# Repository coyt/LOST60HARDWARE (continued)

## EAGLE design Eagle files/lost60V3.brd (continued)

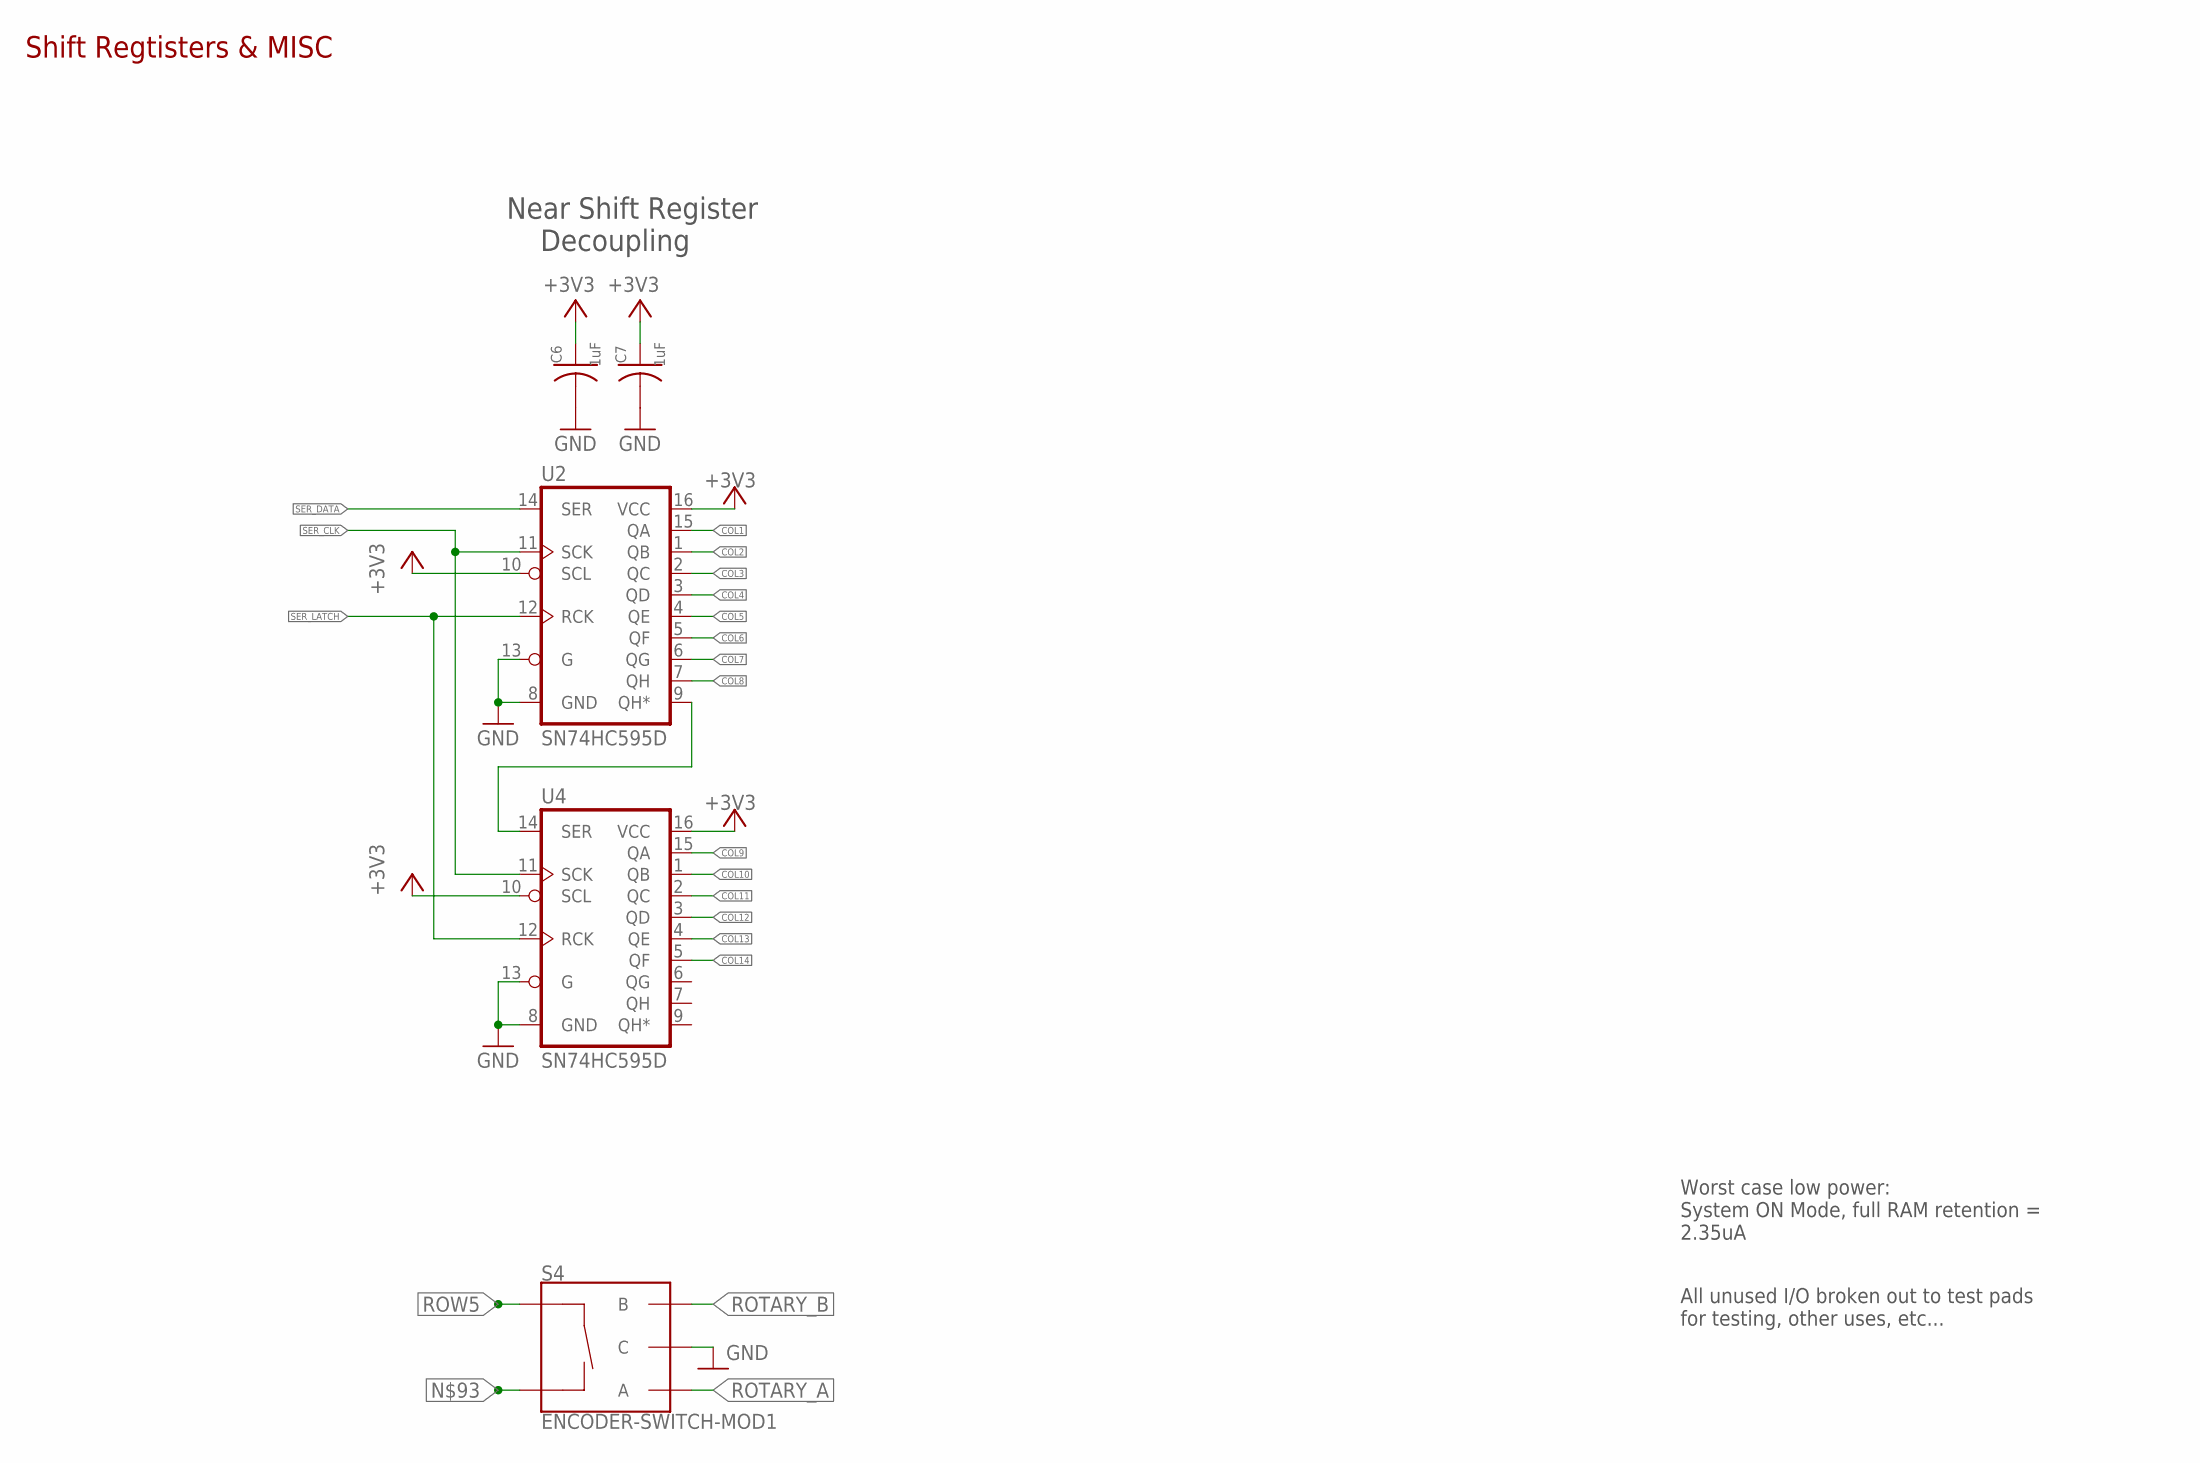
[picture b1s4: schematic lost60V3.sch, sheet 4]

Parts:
C6, C7: 1uF; C0603K
S4: ENCODER-SWITCH-MOD1; ROTARY_ENC_PLAIN-MOD1
U2, U4: SN74HC595D; SO16

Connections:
+3V3: C6.1, C7.1, U2.10 (SCL), U2.16 (VCC), U4.10 (SCL), U4.16 (VCC); also elsewhere on the board
COL1: U2.15 (QA); also elsewhere on the board
COL2: U2.1 (QB); also elsewhere on the board
COL3: U2.2 (QC); also elsewhere on the board
COL4: U2.3 (QD); also elsewhere on the board
COL5: U2.4 (QE); also elsewhere on the board
COL6: U2.5 (QF); also elsewhere on the board
COL7: U2.6 (QG); also elsewhere on the board
COL8: U2.7 (QH); also elsewhere on the board
COL9: U4.15 (QA); also elsewhere on the board
COL10: U4.1 (QB); also elsewhere on the board
COL11: U4.2 (QC); also elsewhere on the board
COL12: U4.3 (QD); also elsewhere on the board
COL13: U4.4 (QE); also elsewhere on the board
COL14: U4.5 (QF); also elsewhere on the board
GND: C6.2, C7.2, S4.C, U2.8 (GND), U2.13 (G), U4.8 (GND), U4.13 (G); also elsewhere on the board
unnamed: U2.9 (QH*), U4.14 (SER)
unnamed 147: S4.SW-; also elsewhere on the board
ROTARY_A: S4.A; also elsewhere on the board
ROTARY_B: S4.B; also elsewhere on the board
ROW5: S4.SW+; also elsewhere on the board
SER_CLK: U2.11 (SCK), U4.11 (SCK); also elsewhere on the board
SER_DATA: U2.14 (SER); also elsewhere on the board
SER_LATCH: U2.12 (RCK), U4.12 (RCK); also elsewhere on the board

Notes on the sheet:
Shift Regtisters & MISC
All unused I/O broken out to test pads for testing, other uses, etc...
Worst case low power: System ON Mode, full RAM retention = 2.35uA
Near Shift Register Decoupling

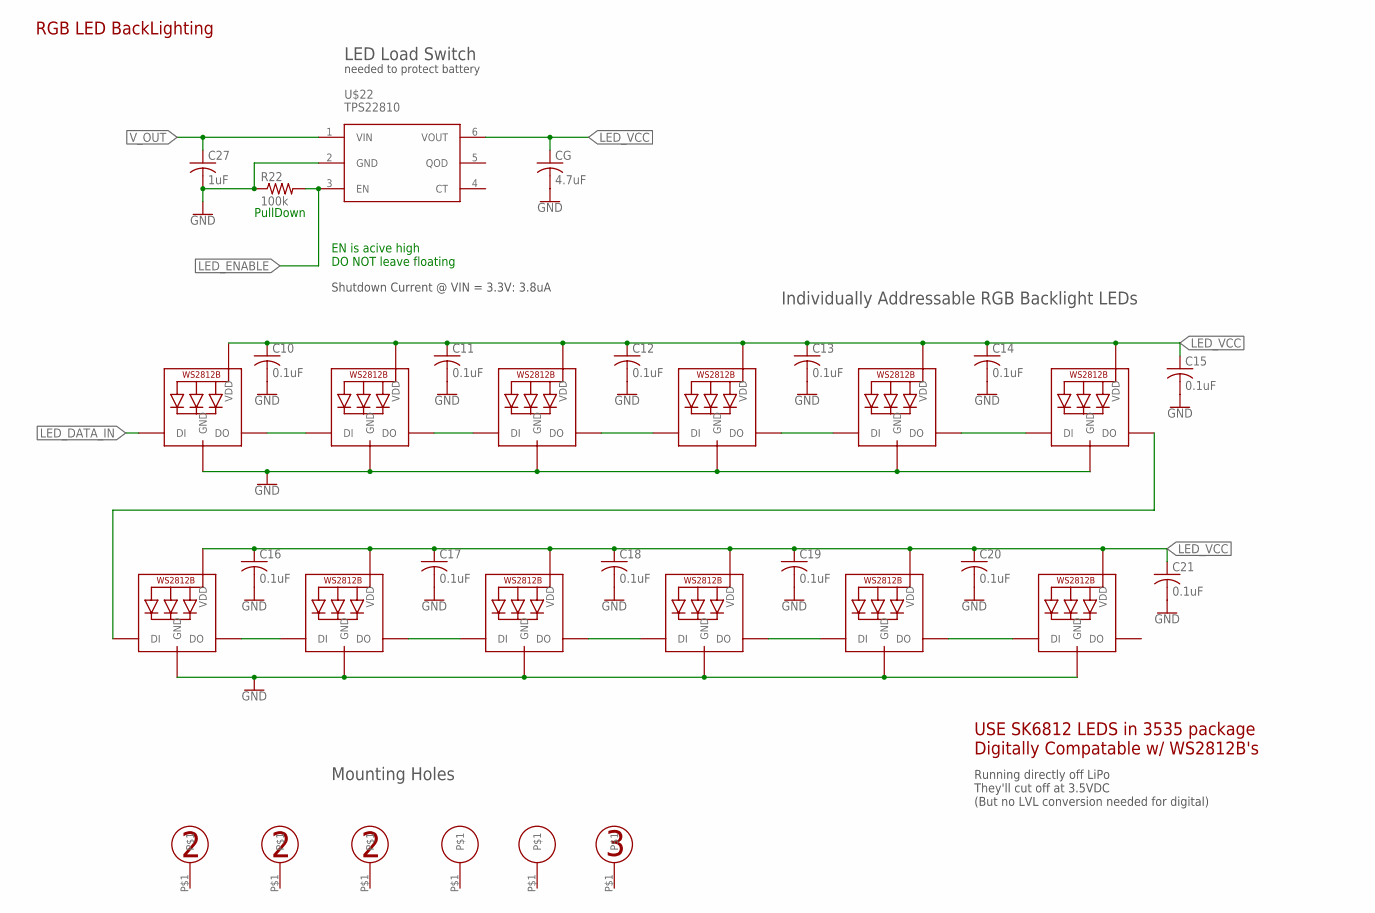
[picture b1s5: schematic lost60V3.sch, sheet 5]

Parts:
C10, C11, C12, C13, C14, C15, C16, C17, C18, C19, C20, C21: 0.1uF; C0603K
C27: 1uF; C0603
CG: 4.7uF; C0603
GND: GH60HOLETYPE3
LED1, LED2, LED3, LED4, LED5, LED6, LED7, LED8, LED9, LED10, LED11, LED12: WS2812B3535; LED3535
R22: 100k; R0603
U$22: TPS22810; SOT23-6
U$125, U$126: GH60HOLE
U$130, U$131, U$132: GH60HOLETYPE2

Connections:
GND: C10.2, C11.2, C12.2, C13.2, C14.2, C15.2, C16.2, C17.2, C18.2, C19.2, C20.2, C21.2, C27.2, CG.2, LED1.4 (GND), LED2.4 (GND), LED3.4 (GND), LED4.4 (GND), LED5.4 (GND), LED6.4 (GND), LED7.4 (GND), LED8.4 (GND), LED9.4 (GND), LED10.4 (GND), LED11.4 (GND), LED12.4 (GND), R22.1, U$22.2 (GND); also elsewhere on the board
LED_DATA_IN: LED4.1 (DI); also elsewhere on the board
LED_ENABLE: R22.2, U$22.3 (EN); also elsewhere on the board
LED_VCC: C10.1, C11.1, C12.1, C13.1, C14.1, C15.1, C16.1, C17.1, C18.1, C19.1, C20.1, C21.1, CG.1, LED1.2 (VDD), LED2.2 (VDD), LED3.2 (VDD), LED4.2 (VDD), LED5.2 (VDD), LED6.2 (VDD), LED7.2 (VDD), LED8.2 (VDD), LED9.2 (VDD), LED10.2 (VDD), LED11.2 (VDD), LED12.2 (VDD), U$22.6 (VOUT)
unnamed: LED1.1 (DI), LED4.3 (DO)
unnamed: LED1.3 (DO), LED3.1 (DI)
unnamed: LED2.1 (DI), LED3.3 (DO)
unnamed: LED2.3 (DO), LED5.1 (DI)
unnamed: LED5.3 (DO), LED6.1 (DI)
unnamed: LED6.3 (DO), LED7.1 (DI)
unnamed: LED7.3 (DO), LED8.1 (DI)
unnamed: LED8.3 (DO), LED9.1 (DI)
unnamed: LED9.3 (DO), LED10.1 (DI)
unnamed: LED10.3 (DO), LED11.1 (DI)
unnamed: LED11.3 (DO), LED12.1 (DI)
V_OUT: C27.1, U$22.1 (VIN); also elsewhere on the board

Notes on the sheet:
USE SK6812 LEDS in 3535 package Digitally Compatable w/ WS2812B's
Running directly off LiPo They'll cut off at 3.5VDC (But no LVL conversion needed for digital)
Mounting Holes
RGB LED BackLighting
Individually Addressable RGB Backlight LEDs
EN is acive high DO NOT leave floating
PullDown
LED Load Switch
needed to protect battery
Shutdown Current @ VIN = 3.3V: 3.8uA

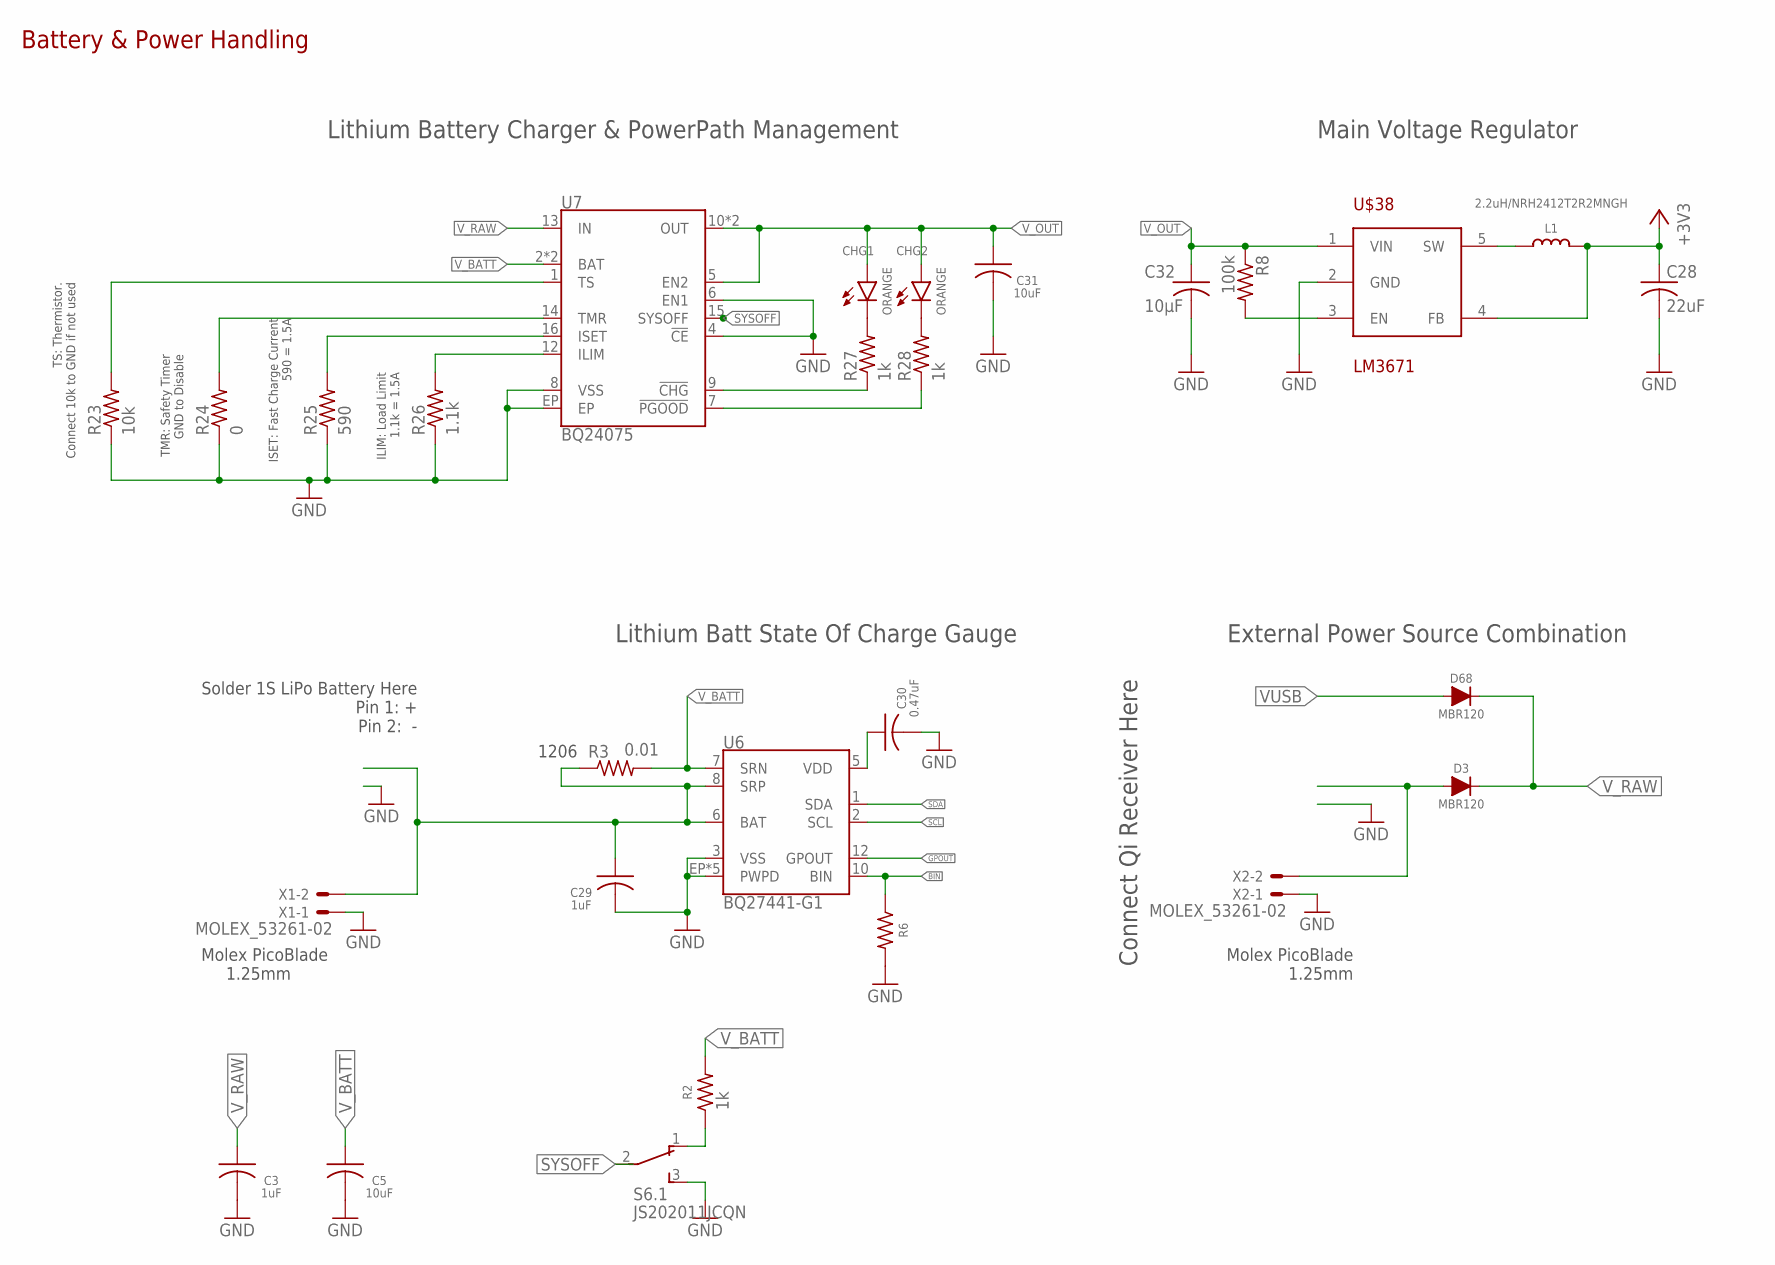
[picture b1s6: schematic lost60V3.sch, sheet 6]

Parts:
C3, C29: 1uF; C0603K
C5, C31: 10uF; C0603K
C28: 22uF; C0603K
C30: 0.47uF; C0603K
C32: 10µF; C0603K
CHG1, CHG2: ORANGE; LED-0603
D3, D68: MBR120; SOD123
L1: 2.2uH/NRH2412T2R2MNGH; MICROBUILDER_INDUCTOR_TAIYOYUDEN_NRH2412T
R2, R27, R28: 1k; R0603
R3: 0.01; R1206
R6: 2.7k; R0603
R8: 100k; R0603
R23: 10k; R0603
R24: 0; R0603
R25: 590; R0603
R26: 1.1k; R0603
S6: JS202011JCQN
U6: BQ27441-G1; PDSO-N12
U7: BQ24075; PVQFN-N16
U$38: LM3671; SOT23-5
X1, X2: MOLEX_53261-02; 53261-02

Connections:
+3V3: C28.1, L1.2, U$38.4 (FB); also elsewhere on the board
BATT_IN: C29.1, R3.1, U6.6 (BAT), U6.8 (SRP), X1.2
BIN: R6.1, U6.10 (BIN)
GND: C3.2, C5.2, C28.2, C29.2, C30.2, C31.2, C32.2, R6.2, R23.1, R24.1, R25.1, R26.1, S6.3 (S), U6.3 (VSS), U6.EP (PWPD), U6.EP1 (PWPD), U6.EP2 (PWPD), U6.EP3 (PWPD), U6.EP4 (PWPD), U7.4 (!CE!), U7.6 (EN1), U7.8 (VSS), U7.EP, U$38.2 (GND), X1.1, X2.1; also elsewhere on the board
GPOUT: U6.12 (GPOUT); also elsewhere on the board
unnamed: R2.1, S6.1 (O)
unnamed: D3.2 (A), X2.2
unnamed: L1.1, U$38.5 (SW)
unnamed: R23.2, U7.1 (TS)
unnamed: R24.2, U7.14 (TMR)
unnamed: C30.1, U6.5 (VDD)
unnamed: R8.2, U$38.3 (EN)
unnamed: R25.2, U7.16 (ISET)
unnamed: R26.2, U7.12 (ILIM)
unnamed: R27.1, U7.9 (!CHG!)
unnamed: CHG1.C, R27.2
unnamed: CHG2.C, R28.2
unnamed: R28.1, U7.7 (!PGOOD!)
SCL: U6.2 (SCL); also elsewhere on the board
SDA: U6.1 (SDA); also elsewhere on the board
SYSOFF: S6.2, U7.15 (SYSOFF)
VUSB: D68.2 (A); also elsewhere on the board
V_BATT: C5.1, R2.2, R3.2, U6.7 (SRN), U7.2 (BAT), U7.3 (BAT)
V_OUT: C31.1, C32.1, CHG1.A, CHG2.A, R8.1, U7.5 (EN2), U7.10 (OUT), U7.11 (OUT), U$38.1 (VIN); also elsewhere on the board
V_RAW: C3.1, D3.1 (C), D68.1 (C), U7.13 (IN)

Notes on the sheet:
Solder 1S LiPo Battery Here Pin 1: + Pin 2: -
Battery & Power Handling
Connect Qi Receiver Here
External Power Source Combination
Lithium Battery Charger & PowerPath Management
Main Voltage Regulator
Lithium Batt State Of Charge Gauge
Molex PicoBlade 1.25mm
1206
TS: Thermistor. Connect 10k to GND if not used
TMR: Safety Timer GND to Disable
ISET: Fast Charge Current 590 = 1.5A
ILIM: Load Limit 1.1k = 1.5A

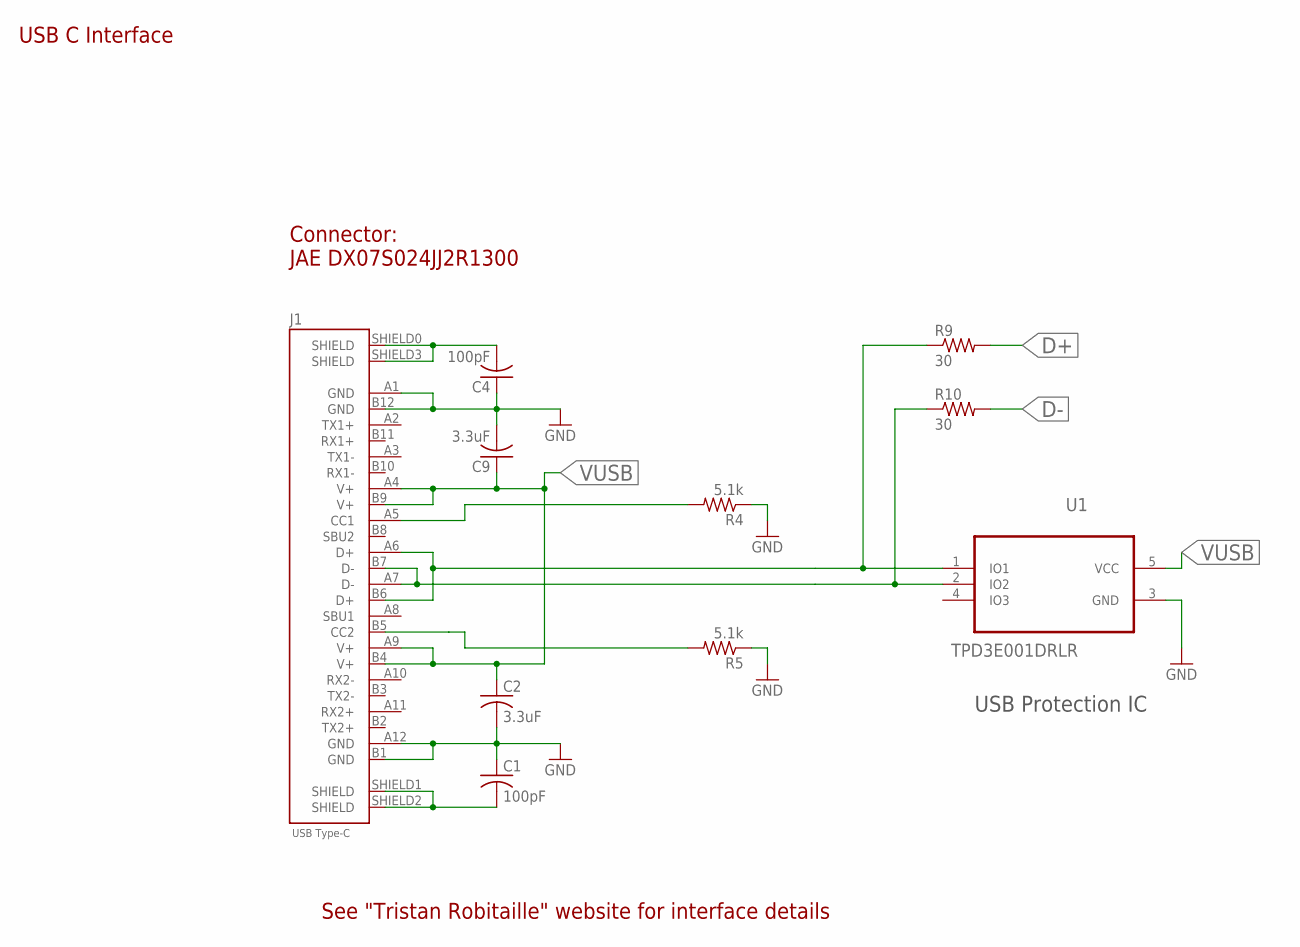
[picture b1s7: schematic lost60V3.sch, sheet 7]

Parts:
C1, C4: 100pF; C0603K
C2, C9: 3.3uF; C0603K
J1: DX07S024JJ2_USB_TYPE-C; DX07S0224JJ2_USB-C
R4, R5: 5.1k; R0603
R9, R10: 30; R0603
U1: TPD3E001DRLR; SOT50P160X60-5N

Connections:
D+: R9.2; also elsewhere on the board
D-: R10.2; also elsewhere on the board
GND: C1.1, C2.2, C4.1, C9.2, J1.A1 (GND), J1.A12 (GND), J1.B1 (GND), J1.B12 (GND), R4.1, R5.1, U1.3 (GND); also elsewhere on the board
unnamed: C4.2, J1.SHIELD0 (SHIELD), J1.SHIELD3 (SHIELD)
unnamed: C1.2, J1.SHIELD1 (SHIELD), J1.SHIELD2 (SHIELD)
unnamed: J1.B5 (CC2), R5.2
unnamed: J1.A7 (D-), J1.B7 (D-), R10.1, U1.2 (IO2)
unnamed: J1.A6 (D+), J1.B6 (D+), R9.1, U1.1 (IO1)
unnamed: J1.A5 (CC1), R4.2
VUSB: C2.1, C9.1, J1.A4 (V+), J1.A9 (V+), J1.B4 (V+), J1.B9 (V+), U1.5 (VCC); also elsewhere on the board

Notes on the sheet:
USB C Interface
Connector: JAE DX07S024JJ2R1300
See "Tristan Robitaille" website for interface details
USB Protection IC

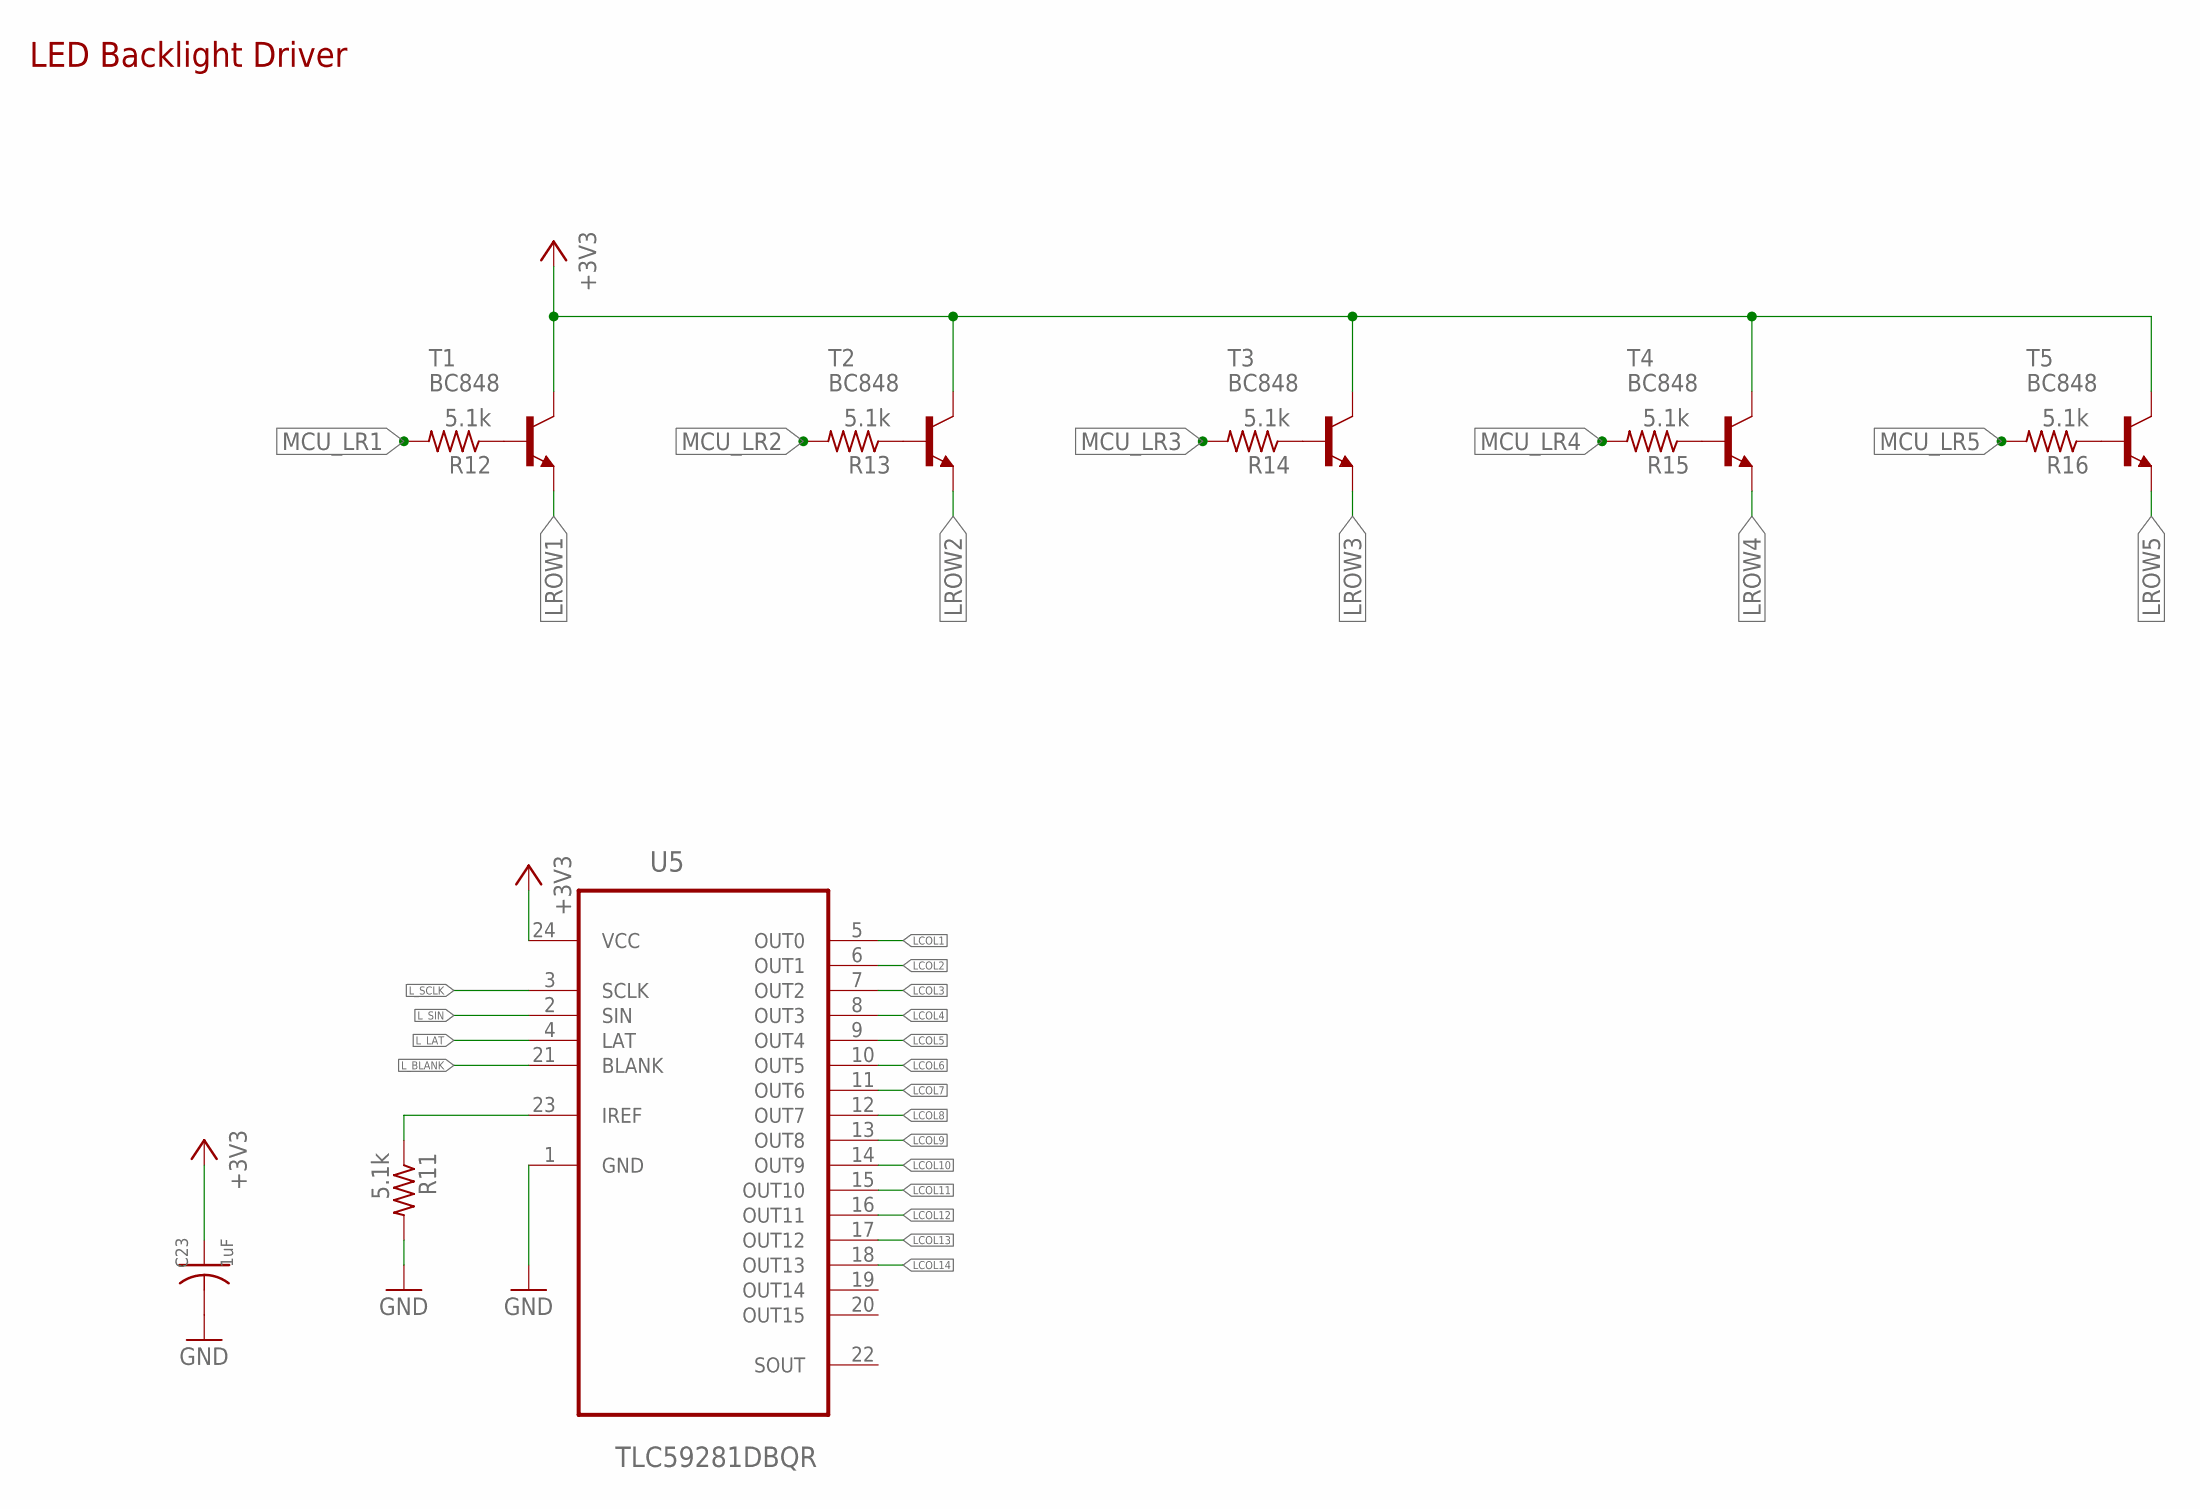
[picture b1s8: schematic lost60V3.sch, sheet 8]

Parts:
C23: 1uF; C0603K
R11, R12, R13, R14, R15, R16: 5.1k; R0603
T1, T2, T3, T4, T5: BC848; SOT23
U5: TLC59281DBQR; SOP63P600X175-28N

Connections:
+3V3: C23.1, T1.3 (C), T2.3 (C), T3.3 (C), T4.3 (C), T5.3 (C), U5.24 (VCC); also elsewhere on the board
GND: C23.2, R11.2, U5.1 (GND); also elsewhere on the board
LCOL1: U5.5 (OUT0); also elsewhere on the board
LCOL2: U5.6 (OUT1); also elsewhere on the board
LCOL3: U5.7 (OUT2); also elsewhere on the board
LCOL4: U5.8 (OUT3); also elsewhere on the board
LCOL5: U5.9 (OUT4); also elsewhere on the board
LCOL6: U5.10 (OUT5); also elsewhere on the board
LCOL7: U5.11 (OUT6); also elsewhere on the board
LCOL8: U5.12 (OUT7); also elsewhere on the board
LCOL9: U5.13 (OUT8); also elsewhere on the board
LCOL10: U5.14 (OUT9); also elsewhere on the board
LCOL11: U5.15 (OUT10); also elsewhere on the board
LCOL12: U5.16 (OUT11); also elsewhere on the board
LCOL13: U5.17 (OUT12); also elsewhere on the board
LCOL14: U5.18 (OUT13); also elsewhere on the board
LROW1: T1.2 (E); also elsewhere on the board
LROW2: T2.2 (E); also elsewhere on the board
LROW3: T3.2 (E); also elsewhere on the board
LROW4: T4.2 (E); also elsewhere on the board
LROW5: T5.2 (E); also elsewhere on the board
L_BLANK: U5.21 (BLANK); also elsewhere on the board
L_LAT: U5.4 (LAT); also elsewhere on the board
L_SCLK: U5.3 (SCLK); also elsewhere on the board
L_SIN: U5.2 (SIN); also elsewhere on the board
MCU_LR1: R12.2; also elsewhere on the board
MCU_LR2: R13.2; also elsewhere on the board
MCU_LR3: R14.2; also elsewhere on the board
MCU_LR4: R15.2; also elsewhere on the board
MCU_LR5: R16.2; also elsewhere on the board
unnamed: R11.1, U5.23 (IREF)
unnamed: R12.1, T1.1 (B)
unnamed: R13.1, T2.1 (B)
unnamed: R14.1, T3.1 (B)
unnamed: R15.1, T4.1 (B)
unnamed: R16.1, T5.1 (B)

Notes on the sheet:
LED Backlight Driver

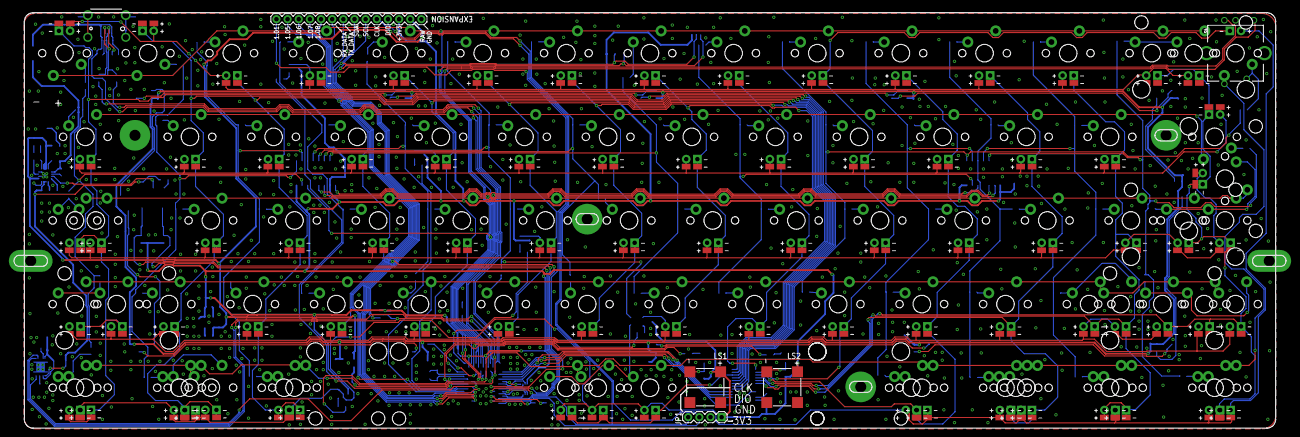
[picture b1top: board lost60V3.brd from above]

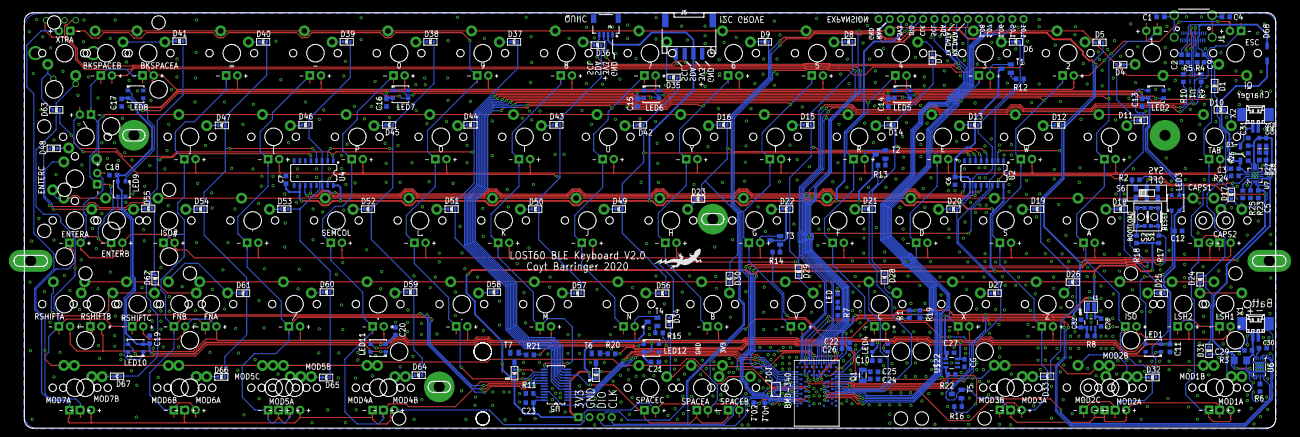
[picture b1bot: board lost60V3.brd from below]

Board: 2 copper layers, 289.7 x 95.4 mm, 268 parts (173 on the bottom side), 200 nets.

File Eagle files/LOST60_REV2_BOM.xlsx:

Qty | Value | Device | Package | Digikey Part Number | Price Per Part | Part Qty. for price | Total Price | Parts | Description
67 |  | DIODESOD-523 | SOD-523 | 1N4448XTPMSCT-ND | 2.3189999999999999E-2 | 1000 | #REF! | D1, D2, D4, D5, D6, D7, D8, D9, D10, D11, D12, D13, D14, D15, D16, D17, D18, D1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 | Diode
1 |  | DX07S024JJ2_USB_TYPE-C | DX07S0224JJ2_USB-C | 670-2794-1-ND | 2.3719999999999999 | 10 | #REF! | J1 | JAE DX07S024JJ2 USB Type-C Connector
1 |  | QWIIC_CONNECTORJS-1MM | 1X04_1MM_RA | 455-1804-1-ND | 0.56899999999999995 | 10 | #REF! | J4 | SparkFun I2C Standard Qwiic Connector
1 | 0 | R-US_R0603 | R0603 | 311-0.0GRCT-ND | 1.9E-2 | 10 | #REF! | R24 | RESISTOR, American symbol
1 | 0.01 | R-US_R1206 | R1206 | 408-1570-1-ND | 0.38500000000000001 | 10 | #REF! | R3 | RESISTOR, American symbol
12 | 0.1uF | C-USC0603K | C0603K | 399-1099-1-ND | 1.1520000000000001E-2 | 500 | #REF! | C10, C11, C12, C13, C14, C15, C16, C17, C18, C19, C20, C21 | CAPACITOR, American symbol
1 | 0.47uF | C-USC0603K | C0603K | 1276-2082-1-ND | 7.2999999999999995E-2 | 10 | #REF! | C30 | CAPACITOR, American symbol
1 | 1.1k | R-US_R0603 | R0603 | RMCF0603FT1K10CT-ND | 1.6E-2 | 10 | #REF! | R26 | RESISTOR, American symbol
2 | 100k | R-US_R0603 | R0603 | RR08P100KDCT-ND | 9.2999999999999999E-2 | 10 | #REF! | R8, R22 | RESISTOR, American symbol
2 | 100pF | C-USC0603K | C0603K | 1292-1644-1-ND | 2.8000000000000001E-2 | 10 | #REF! | C1, C4 | CAPACITOR, American symbol
3 | 10k | R-US_R0603 | R0603 | 311-10KGRCT-ND | 1.9E-2 | 10 | #REF! | R17, R18, R23 | RESISTOR, American symbol
3 | 10uF | C-USC0603K | C0603K | 587-5869-1-ND | 4.5100000000000001E-2 | 100 | #REF! | C5, C26, C31,C32 | CAPACITOR, American symbol
2 | 15pF | C-USC0603K | C0603K | 1292-1487-1-ND | 2.8000000000000001E-2 | 10 | #REF! | C24, C25 | CAPACITOR, American symbol
2 | 4.7k | R-US_R0603 | R0603 | 311-4.7KGRCT-ND | 1.9E-2 | 10 | #REF! | R1, R19
4 | 1k | R-US_R0603 | R0603 | 311-1.0KGRCT-ND | 7.7000000000000002E-3 | 100 | #REF! | R2, R7, R27, R28 | RESISTOR, American symbol
6 | 1uF | C-USC0603K | C0603K | 1276-6524-1-ND | 1.8599999999999998E-2 | 100 | #REF! | C3, C6, C7, C22, C23, C27, C29 | CAPACITOR, American symbol
1 | 2.2uH/NRH2412T2R2MNGH | MICROBUILDER_INDUCTORNRH2412T | MICROBUILDER_INDUCTOR_TAIYOYUDEN_NRH2412T | 587-3443-1-ND | 0.20300000000000001 | 10 | #REF! | L1 | Inductors
1 | 2.7k | R-US_R0603 | R0603 | A129693CT-ND | 0.03 | 10 | #REF! | R6 | RESISTOR, American symbol
1 | 22uF | C-USC0603K | C0603K | 1276-2868-1-ND | 0.17299999999999999 | 10 | #REF! | C28 | CAPACITOR, American symbol
2 | 3.3uF | C-USC0603K | C0603K | 399-5502-1-ND | 0.17100000000000001 | 10 | #REF! | C2, C9 | CAPACITOR, American symbol
2 | 30 | R-US_R0603 | R0603 | 311-30GRCT-ND | 1.9E-2 | 10 | #REF! | R9, R10 | RESISTOR, American symbol
1 | 32.768kHz | KX-327-NHF | 3.2X1.5 | 300-8879-1-ND | 0.44600000000000001 | 10 | #REF! | Q1 | Tuning Fork Crystals (kHz) SMD:
1 | 4.7uF | C-USC0603 | C0603 | 1276-1045-1-ND | 5.5E-2 | 10 | #REF! | CG | CAPACITOR, American symbol
10 | 5.1k | R-US_R0603 | R0603 | P5.10KHCT-ND | 2.3400000000000001E-2 | 100 | #REF! | R4, R5, R11, R12, R13, R14, R15, R16, R20, R21 | RESISTOR, American symbol
1 | 590 | R-US_R0603 | R0603 | 311-590HRCT-ND | 2.3E-2 | 10 | #REF! | R25 | RESISTOR, American symbol
7 | BC848 | BC848 | SOT23 | BC848BLT1GOSCT-ND | 0.11600000000000001 | 10 | #REF! | T1, T2, T3, T4, T5, T6, T7 | NPN TRANSISTOR
1 | BMD-340 | BMD-340 | BMD-340 | 672-BMD-340-A-R-00CT-ND | 12.07 | 10 | #REF! | BMD-340
1 | BQ24075 | BQ24075 | PVQFN-N16 | 296-25609-1-ND | 2.0419999999999998 | 10 | #REF! | U7 | Texas Instruments BQ24075 LiPo Battery Chargerand Power-Path Management IC
1 | BQ27441-G1 | BQ27441-G1 | PDSO-N12 | 296-39941-1-ND | 2.3530000000000002 | 10 | #REF! | U6 | Texas Instruments BQ27441-G1 LiPo Battery Fuel Gauge
2 | CMT-8530S-SMT | CMT-8530S-SMT | CUI_CMT-8530S-SMT | 102-3736-1-ND | 2.202 | 25 | #REF! | LS1, LS2 | 8.5 mm, 3.6 Vo-p, 90 dB, Surface Mount (SMT), Magnetic Audio Transducer Buzzer
1 | GD25Q16CEIGR | MICROBUILDER_SPIFLASH_8PINUX | MICROBUILDER_USON8 | 1970-1011-1-ND | 0.55200000000000005 | 10 | #REF! | U3 | SOIC8 SPI Flash
1 | LM3671 | LM3671 | SOT23-5 | LM3671MF-3.3/NOPBCT-ND | 1.282 | 10 | #REF! | U$38 | Texas Instruments LM3671, LM3671Q 2MHz, 600mA Step-Down DC-DC Converter
2 | MBR120 | D-FILL-SOD123 | SOD123 | SL22PL-TPMSCT-ND | 0.313 | 10 | #REF! | D3, D68 | DIODE
2 | MOLEX_53261-02 | MOLEX_53261-02 | 53261-02 | WM7620CT-ND | 0.86 | 10 | #REF! | X1, X2 | CONNECTOR
2 | MOMENTARY-SWITCH-SPST-SMD-4.6X2.8MM | MOMENTARY-SWITCH-SPST-SMD-4.6X2.8MM | TACTILE_SWITCH_SMD_4.6X2.8MM | CKN11065CT-ND | 0.432 | 10 | #REF! | S1, S2 | Momentary Switch (Pushbutton) - SPST
2 | ORANGE | LED0603 | LED-0603 | SML-D12D1WT86CT-ND | 0.155 | 10 | #REF! | CHG1, CHG2 | LED (Generic)
1 | RED | LED0603 | LED-0603 | 732-4978-1-ND | 0.14000000000000001 | 1 | #REF! | LED | LED (Generic)
2 | SN74HC595D | 74HC595D | SO16 | 296-14857-1-ND | 0.34 | 10 | #REF! | U2, U4 | 8-Bit Shift Register (Serial to Parallel)
1 | TLC59281DBQR | TLC59281DBQR | SOP63P600X175-28N | 296-25789-6-ND | 1.149 | 10 | #REF! | U5 | 16-Channel LED Driver
1 | TPD3E001DRLR | TPD3E001DRLR | SOT50P160X60-5N | 296-21885-1-ND | 0.433 | 10 | #REF! | U1 | LOW-CAPACITANCE 3-CHANNEL Â±15-kV ESD-PROTECTION ARRAY FOR HIGH-SPEED DATA INTE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
1 | TPS22810* | TPS22810* | SOT23-6 | 296-45297-1-ND | 0.54500000000000004 | 10 | #REF! | U$22 | The TPS22810 is a single channel load switch with
1 | 4P-SMD-2.0-90D | GROVE-CONNECTOR-SMD-90D(4+2P-2.0) | HW4-SMD-2.0-90D |  |  |  | #REF! | J5 | 320110032
1 | JS202011JCQN | JS202011JCQN | JS202011JCQN |  |  |  | #REF! | S6
12 | WS2812B3535 | WS2812B3535 | LED3535 |  |  |  | #REF! | LED1, LED2, LED3, LED4, LED5, LED6, LED7, LED8, LED9, LED10, LED11, LED12
1 | ENCODER-SWITCH-MOD1 | ENCODER-SWITCH-MOD1 | ROTARY_ENC_PLAIN-MOD1 | PEC11R-4220K-S0024-ND | 1.56600 | 10 | #REF! | S4 | Rotary Encoder w/ Select Switch
1 |  | M14 | 1X14 |  |  |  | #REF! | JP2 | Header 14
 | Top components: | 95
 | Bottom components: | 173 |  |  |  |  | #REF!
 | Total Pads: | 1124

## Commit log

2020-04-19 initial add of media and design files
2020-04-19 started fixing up readme and adding media properly
2020-04-19 fixed more pictures
2020-04-19 fixed more pics
2020-04-19 added bill of materials
2020-04-19 more pics
